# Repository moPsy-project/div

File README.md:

# DIV

> Simple Counter/Divider Eurorack Module

## Dependencies

This project uses symbols from the [moPsy-KiCad-resources](https://github.com/moPsy-project/moPsy-KiCad-resources).

## License

This work is licensed under a [Creative Commons Attribution-ShareAlike 4.0 International License](http://creativecommons.org/licenses/by-sa/4.0/).

BY: Stefan Haun (mail@tuxathome.de)

See [LICENSE.txt](LICENSE.txt) for details.

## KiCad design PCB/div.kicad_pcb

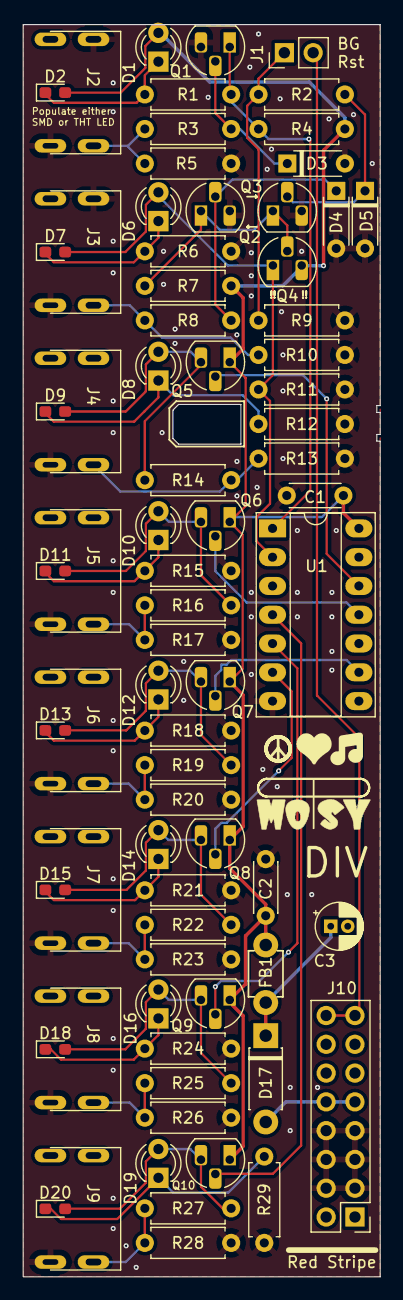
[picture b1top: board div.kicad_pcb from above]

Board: 2 copper layers, 31.5 x 110.5 mm, 74 parts (0 on the bottom side), 40 nets.

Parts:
C1, C2: 100n; C_Disc_D4.3mm_W1.9mm_P5.00mm
C3: 10u; CP_Radial_D4.0mm_P1.50mm
D1: ye; LED_D3.0mm
D2, D7, D9, D11, D13, D15, D18, D20: gn; LED_0603_1608Metric_Pad1.05x0.95mm_HandSolder
D3, D4, D5: 1N4148; D_DO-35_SOD27_P5.08mm_Horizontal
D6: rt; LED_D3.0mm
D8, D10, D12, D14, D16, D19: gn; LED_D3.0mm
D17: 1N5817; D_DO-41_SOD81_P7.62mm_Horizontal
FB1: FerriteBead; FBeadL4D4
J1: Bus Gate Reset; PinHeader_1x02_P2.54mm_Vertical
J2: Clk; CLIFF 3.5mm S6 Mono Jack Socket
J3: Rst; CLIFF 3.5mm S6 Mono Jack Socket
J4, J5, J6, J7, J8, J9: OUT; CLIFF 3.5mm S6 Mono Jack Socket
J10: PWR; PinHeader_2x08_P2.54mm_Vertical
Q1, Q2, Q3, Q5, Q6, Q7, Q8, Q9, Q10: BC547; TO-92_HandSolder
Q4: BC557; TO-92_HandSolder
R1, R2, R3, R4, R6, R7, R8, R11, R12, R15, R18, R21, R24, R29: 10k; R_Axial_DIN0207_L6.3mm_D2.5mm_P7.62mm_Horizontal
R5, R9, R10: 1M; R_Axial_DIN0207_L6.3mm_D2.5mm_P7.62mm_Horizontal
R13, R14, R16, R17, R19, R20, R22, R23, R25, R26, R27, R28: 2k2; R_Axial_DIN0207_L6.3mm_D2.5mm_P7.62mm_Horizontal
U1: 4024; DIP-14_W7.62mm_Socket_LongPads

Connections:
+12V: C1.1, C2.1, D1.2 (A), D2.2 (A), FB1.2, Q4.3 (E), Q5.1 (C), Q6.1 (C), Q7.1 (C), Q8.1 (C), Q9.1 (C), Q10.1 (C), R4.2, R7.2, U1.14 (VDD)
/CLOCK_IN: Q1.1 (C), R1.1, R4.1, U1.1 (~CLK)
/Gate Output 2/GATE_OUT: Q5.2 (B), U1.12 (Q0)
/Gate Output 4/GATE_OUT: Q6.2 (B), U1.11 (Q1)
/Gate Output 8/GATE_OUT: Q7.2 (B), U1.9 (Q2)
/Gate Output 16/GATE_OUT: Q8.2 (B), U1.6 (Q3)
/Gate Output 32/GATE_OUT: Q9.2 (B), U1.5 (Q4)
/Gate Output 64/GATE_OUT: Q10.2 (B), U1.4 (Q5)
/RESET_IN: D6.2 (A), D7.2 (A), Q4.1 (C), R11.2, U1.2 (MR)
GND: C1.2, C2.2, C3.2, D3.2 (A), D4.2 (A), D5.2 (A), J2.S, J2.TN, J3.S, J3.TN, J4.S, J5.S, J6.S, J7.S, J8.S, J9.S, J10.3, J10.4, J10.5, J10.6, J10.7, J10.8, Q1.3 (E), Q2.3 (E), Q3.3 (E), R5.1, R6.1, R9.1, R10.1, R11.1, R12.1, R13.1, R15.1, R17.1, R18.1, R20.1, R21.1, R23.1, R24.1, R26.1, R28.1, R29.1, U1.7 (VSS)
Gate: J1.2, J10.15, J10.16
unnamed: D1.1 (K), D2.1 (K), R1.2
unnamed: D3.1 (K), Q1.2 (B), R3.2
unnamed: D4.1 (K), Q2.2 (B), R8.2
unnamed: D5.1 (K), Q3.2 (B), R2.2
unnamed: D6.1 (K), D7.1 (K), R6.2
unnamed: D8.2 (A), D9.2 (A), Q5.3 (E), R14.2
unnamed: D8.1 (K), D9.1 (K), R12.2
unnamed: D10.2 (A), D11.2 (A), Q6.3 (E), R16.2
unnamed: D10.1 (K), D11.1 (K), R15.2
unnamed: D12.2 (A), D13.2 (A), Q7.3 (E), R19.2
unnamed: D12.1 (K), D13.1 (K), R18.2
unnamed: D14.2 (A), D15.2 (A), Q8.3 (E), R22.2
unnamed: D14.1 (K), D15.1 (K), R21.2
unnamed: D16.2 (A), D18.2 (A), Q9.3 (E), R25.2
unnamed: D16.1 (K), D18.1 (K), R24.2
unnamed: D17.2 (A), J10.9, J10.10
unnamed: C3.1, D17.1 (K), FB1.1
unnamed: D19.2 (A), D20.2 (A), Q10.3 (E), R27.2
unnamed: D19.1 (K), D20.1 (K), R29.2
unnamed: J1.1, R2.1, R9.2
unnamed: J2.T, R3.1, R5.2
unnamed: J3.T, R8.1, R10.2
unnamed: J4.T, R13.2, R14.1
unnamed: J5.T, R16.1, R17.2
unnamed: J6.T, R19.1, R20.2
unnamed: J7.T, R22.1, R23.2
unnamed: J8.T, R25.1, R26.2
unnamed: J9.T, R27.1, R28.2
unnamed: Q2.1 (C), Q3.1 (C), Q4.2 (B), R7.1

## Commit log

2023-04-03 :tada: Initial commit
2023-04-03 :money_with_wings: Add FUNDING information
2023-04-03 :construction_worker: Add release workflow
2023-04-03 :see_no_evil: Add gitignore for KiCAD projects
2023-04-03 :tada: Add KiCAD PCB project
2023-04-03 :sparkles: Add Power connection
2023-04-03 :sparkles: Add Gate output element
2023-04-03 :sparkles: Add count and reset input
2023-04-03 :sparkles: Add the counter logic
2023-04-03 :sparkles: Add bus gate reset option
2023-04-07 :wrench: Add moPsy footprint library
2023-04-07 :wrench: Set CLIFF footprints for the jacks
2023-04-07 :memo: Change module name in README
2023-04-07 :truck: Rename KiCad project to "div"
2023-04-07 :wrench: Adjust project name on sheets
2023-04-07 :sparkles: Add the non-text print for the frontpanel
2023-04-07 :sparkles: Add an outline sketch for the frontpanel
2023-04-07 :bento: Export outline to DXF
2023-04-07 :sparkles: Add the frontpanel PCB with LED holes
2023-04-07 :sparkles: Add the frontpanel PCB without LED holes
2023-04-13 :bug: Fix reset input circuit
2023-04-13 :wrench: Adjust LED series resistors
    With 4k7 the brightness is much better to look at.
2023-04-14 :hammer: Switch circuit to 12V supply
2023-04-14 :hammer: Change output gate for 12V
    Add a resistor divider to create about 5V for the gate output.
2023-04-18 :art: Improve reset input to drive 12V
2023-04-18 :art: Remove base resistor from output stage
    The emitter follower does not need a base resistor.
    Current has been measured at 11µA if the output is shorted to ground.
2023-04-18 :art: Add separate transistor stage for the bus reset input
    This resolves the problems of backdriving and unwanted resistor
    dividers between jack and bus input.
2023-04-18 :pencil2: Fix naming of ferrite bead footprint
2023-04-18 :sparkles: Add symbol annotations
2023-04-18 :hammer: Optimize schematic for PCB layout
2023-04-18 :sparkles: Add first PCB layout
2023-04-20 :sparkles: Add jack LEDs to the schematic
    Using clear jacks the LEDs can be put underneath them. The control
    PCB can support both versions (LEDs separate or in jacks), so a
    second (SMD) LED is added to the schematic.
    Only one of these may be populated!
2023-04-20 :sparkles: Add SMD LEDs to PCB
2023-04-20 :hammer: Change power connector footprint in schematic
2023-04-20 :hammer: Adapt PCB to vertical header and turn red stripe down
2023-04-20 :art: Leave more room around the power connector
    This is needed for the box header.
2023-05-04 :hammer: Extend frontpanel copper layer to front and back side
2023-05-04 :bento: Add a picture of the built module in a rack
    This is module v1
2023-05-04 :memo: Add module picture to the README
2023-05-05 :wrench: Adjust output resistor divider
    Give a bit more driving power to the outputs by lowering the output
    resistor divider.
    This results in a current of 2.7mA through the resistor divider
    or 5.5mA in case of a short circuit.
    With all outputs switched on, consumption is 16.3mA
    (32.7mA short ciruit).
2023-05-05 :wrench: Increase input resistors to improve impedance
    Set the input resistors to 100K to improve input impedance.
2023-05-16 :bento: Update PCB to set correct resistor values
    In #20 the resistor values have been changed in the schematic.
    As this was no PCB change, I did not mind to update the PCB file. However,
    the old resistor values are now shown there and also in the BOM.
    This is only an update to the resistor values stored in the PCB file, no changes
    to the actual PCB layout have been made.
2023-05-16 :arrow_up: Update runner in the release workflow
    The runner ubuntu-18.04 is no longer available.
    As the version is not really important, run this workflow on ubuntu-latest.
2023-05-16 :wrench: Change transistor footprint to handsolder version
2023-05-16 :wrench: Adjust PCB to changed transistor footprint
2023-05-16 :sparkles: Add an LED bending gauge
    Allows to bend the LEDs exactly while building the module.
2023-05-16 :art: Add a pull-down resistor to the clock input
    Keep this input from floating when only one end of the patch cable
    is connected by adding a (very large) pull-down resistor.
2023-05-16 :art: Add a pull-down resistor to open bus gate reset
    If the jumper is not set, the bus gate reset would be floating. Add a
    (very large) pull-down resistor to keep this at GND.
2023-05-16 :art: Add a pull-down resistor to the reset input
    Attaching a cable and touching the other end triggers the reset.
    Add a (very large) pull-down resistor to prevent the line from
    floating.
2023-05-16 :memo: Update sheet meta-data for revision 1.1
2023-05-16 :memo: Change PCB text to v1.1
2023-05-16 :art: Change the diode footprint to make soldering easier
2023-05-16 :art: Move C1 slightly for a more relaxed fit with the power connector
2023-05-16 :lipstick: Duplicate the "Red Stripe" marker to the bottom silk screen
    The front marker might be covered by the socket.
2023-05-16 :lipstick: Fix designator positions for Q9 and Q10
2023-05-16 :pencil2: Fix relevant DRC warnings
2023-05-16 :adhesive_bandaid: Fix DRC errors
    Display of errors was accidentally switched off und with the change
    of transistor footprints trace overlaps have been introduced.
    These errors are now fixed.
2023-05-16 :lipstick: Perform a Geographical Reannotation on the PCB
2023-05-16 :lipstick: Fix designator positions
    Some designators changed size as the number of digits changed.
    Fix their positions to avoid overlaps and ensure readability.
2023-05-16 :sparkles: Add text areas for builder and S/N
2023-05-16 :lipstick: Unify positions of diode designators
2023-05-16 :adhesive_bandage: Fix direction of LED gauge
2023-05-17 :wrench: Revert input resistors to 10K
    Test built with SMD LEDs shows that the 100K base resistor does not
    open the transistors sufficiently. Change back to 10K for robust
    operation.
    The problem that occurred: With lower LED series resistors (220R) the
    transistor would be part of a voltage divider leading to 6V output,
    which is not enough to trigger the 4024 clock input.
2023-05-17 :lipstick: Re-arrange logos
2023-05-17 :lipstick: Change color of non-LED board and add "glow"
2023-05-17 :memo: Change frontpanel release to v1.1
2023-05-19 :wrench: Change LED footprint to 0603
    This is harder to solder, but matching LEDs with 180mcd are available:
    * https://www.reichelt.de/led-smd-1608-0603-rot-180-mcd-120--led-el-0603-rt-p156256.html
    * https://www.reichelt.de/led-smd-1608-0603-gelb-180-mcd-120--led-el-0603-ge-p156259.html
2023-06-05 :memo: Update picture to show DIV glow as well
2023-06-05 :bento: Add picture of case shot with DIV glow variant
2023-06-06 :bento: Add moPsy assets
2023-06-06 :bento: Add PGN exports of F/B silk and frontpanel layer
2023-06-06 :sparkles: Add the assembly guide (tex)
2023-06-06 :art: Write resistor value consistent with other values
2023-06-06 :sparkles: Add an e-mail address
2023-06-06 :art: Replace "moPsy" by moPsy logo
2023-06-06 :art: Improve introduction (rating mostly)
2023-06-06 :bento: Add moPsy resources
2023-06-06 :bento: Add figure for frontpanel with labels
2023-06-06 :bento: Add figure for Bus Reset jumper position
2023-06-06 :sparkles: Add the DIV user manual (tex)
2023-06-06 :bento: Add case shot with frame
2023-06-06 :bento: Add silkscreen SVG exports
    PNG file are just exports of these. Add the SVG files to make later changes easier
2023-06-06 :bento: Update PNG exports according to SVG
2023-06-06 :pencil2: Fix change aspect number in assembly guide
    "two" → "three"
2023-06-07 :hammer: Change online resources to mopsy website link
2023-06-24 :pencil2: Fix the number of steps the module can handle
2023-06-24 :art: Improve the module description
    Based on what has been used on the module homepage.

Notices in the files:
PCB/div.kicad_pcb:
CC BY-SA 4.0
